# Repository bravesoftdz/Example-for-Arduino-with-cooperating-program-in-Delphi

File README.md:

# Example-for-Arduino-with-cooperating-program-in-Delphi
Example sketch for different Arduino equipment with cooperating program in Delphi for YouTube presentation

This examples I tested for four modules

Arduino Uno + Ethernet shield with expander PCF 8574N port, which is shown in this lesson.
Nodemcu Wifi ESP8266 v2 and v3 (Lolino) - with two expanders PCF8574N Topic of the next lesson
Nodemcu Wifi ESP8266 v2 and v3 (Lolino) - with MCP 23017 16 port expander. In the same lesson you will see the Wemos D1 MINI pro Wifi board as it is compatible with NodeMcu. You just have to make the right adapter. Subject of the next lesson.
Wemos MEGA Wifi plate . - in the plan. The next lesson.

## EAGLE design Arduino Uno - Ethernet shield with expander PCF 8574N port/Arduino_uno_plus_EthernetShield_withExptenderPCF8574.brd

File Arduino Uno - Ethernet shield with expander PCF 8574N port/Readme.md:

Lesson 1. 
  
  by polish Arduino Uno + Ethernet z ekspanderem portów PCF 8574N - ten podkatalog zawiera
           shield dla tych urządzen  i programu exe współpracującym z tym sketch-em .
           Także jest obecne tutaj źródło tego programu w Delphi. Dla tego sketch-u
           jest tutaj dodatkowa bilblioteka do rozszerzenia portów PCF8574 8 portów w 
           postacipliku zip . Uzytkownik może miec kłopty z tą biblioteką .

  by english .Arduino Uno + Ethernet shield with expander PCF 8574N port - this branch contain 
          shield for this equiment and program exe cooerating with this sketch
          also there is present source for program in Delphi . For this is sketch 
          is presnt additional libray for extender PCF8574 8 ports in a zip file . 
          This is because with this libray user can have trouble

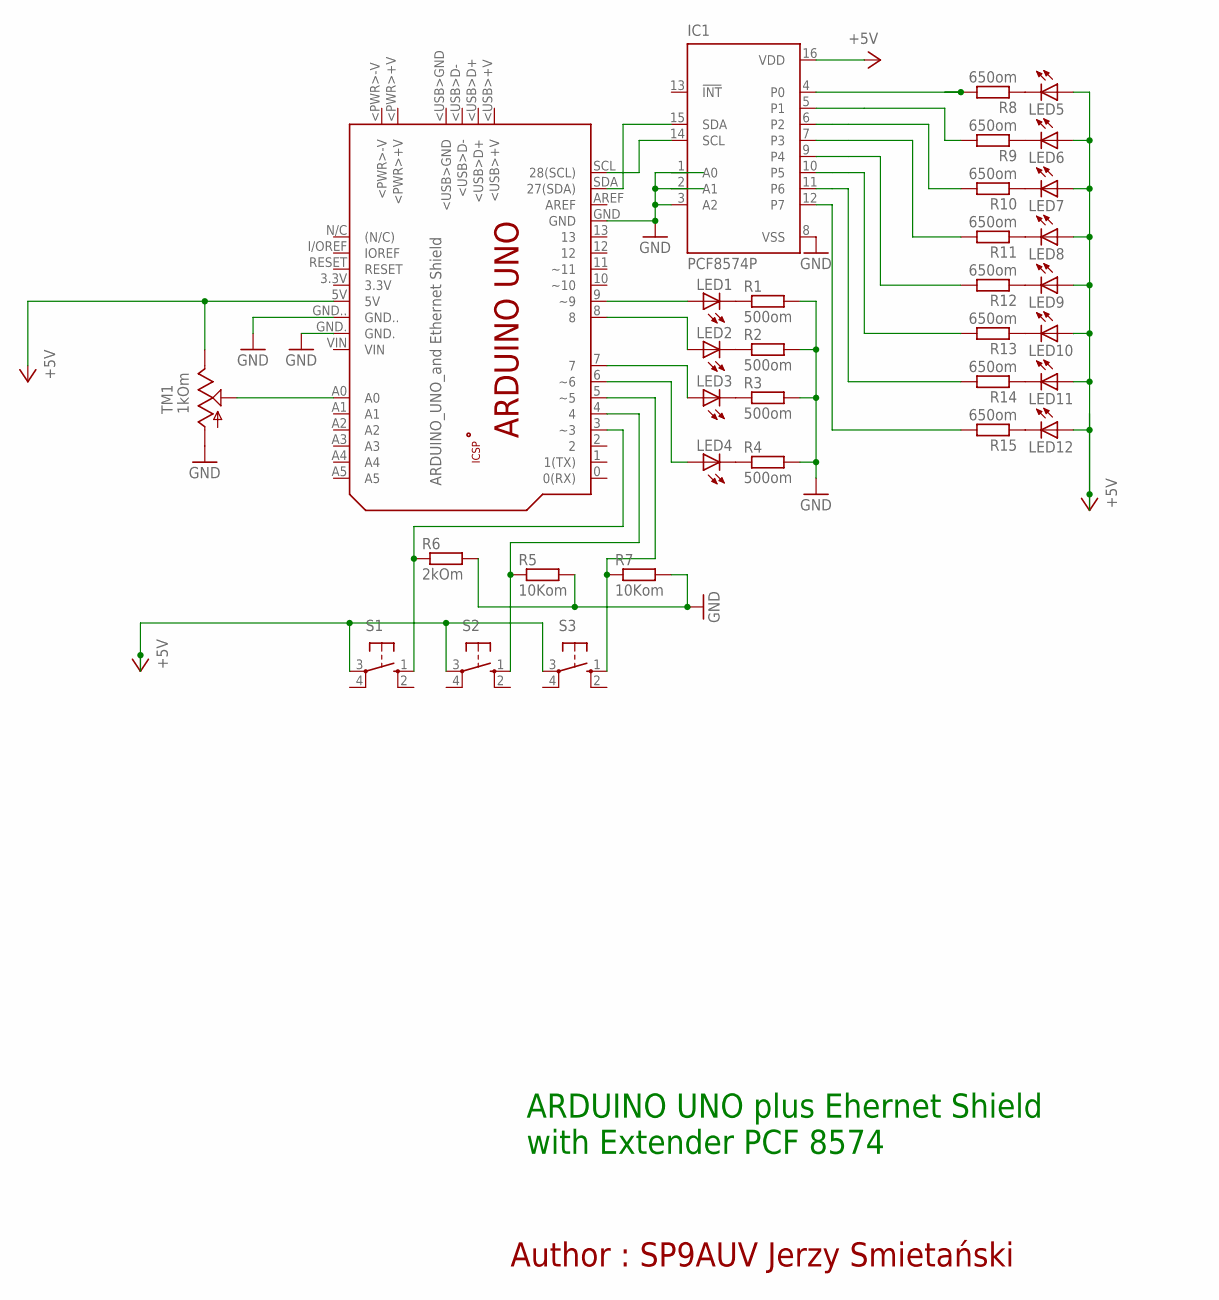
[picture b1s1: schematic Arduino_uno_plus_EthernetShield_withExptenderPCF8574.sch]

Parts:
ARDUINO_UNO: ARDUINO_U1; ARDUINO_UNO
IC1: PCF8574P; DIL16
LED1, LED2, LED3, LED4, LED5, LED6, LED7, LED8, LED9, LED10, LED11, LED12: LEDSQR2X5; LED2X5
R1, R2, R3, R4: 500om; 0204/5
R5, R7: 10Kom; 0204/5
R6: 2kOm; 0204/5
R8, R9, R10, R11, R12, R13, R14, R15: 650om; 0204/5
S1, S2, S3: 10-XX; B3F-10XX
TM1: 1kOm; 6MM

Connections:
+5V: ARDUINO_UNO.5V, IC1.16 (VDD), LED5.A, LED6.A, LED7.A, LED8.A, LED9.A, LED10.A, LED11.A, LED12.A, S1.3, S2.3, S3.3, TM1.E
GND: ARDUINO_UNO.GND, ARDUINO_UNO.GND.., IC1.2 (A1), IC1.3 (A2), IC1.8 (VSS), R1.2, R2.2, R3.2, R4.2, R5.2, R6.2, R7.2
GND1: IC1.5 (P1), R9.2
unnamed: ARDUINO_UNO.A0, TM1.S
unnamed: ARDUINO_UNO.GND., TM1.A
unnamed: LED1.K (C), R1.1
unnamed: LED2.K (C), R2.1
unnamed: LED3.K (C), R3.1
unnamed: LED4.K (C), R4.1
unnamed: ARDUINO_UNO.9 (~9), LED1.A
unnamed: ARDUINO_UNO.8, LED2.A
unnamed: ARDUINO_UNO.7, LED3.A
unnamed: ARDUINO_UNO.3 (~3), R6.1, S1.1 (S)
unnamed: ARDUINO_UNO.6 (~6), LED4.A
unnamed: ARDUINO_UNO.5 (~5), R7.1, S3.1 (S)
unnamed: ARDUINO_UNO.4, R5.1, S2.1 (S)
unnamed: IC1.12 (P7), R15.2
unnamed: IC1.7 (P3), R11.2
unnamed: IC1.6 (P2), R10.2
unnamed: IC1.4 (P0), R8.2
unnamed: LED5.K (C), R8.1
unnamed: LED6.K (C), R9.1
unnamed: LED7.K (C), R10.1
unnamed: LED8.K (C), R11.1
unnamed: IC1.10 (P5), R13.2
unnamed: IC1.9 (P4), R12.2
unnamed: ARDUINO_UNO.SCL (28(SCL)), IC1.14 (SCL)
unnamed: ARDUINO_UNO.SDA (27(SDA)), IC1.15 (SDA)
unnamed: LED9.K (C), R12.1
unnamed: LED10.K (C), R13.1
unnamed: LED11.K (C), R14.1
unnamed: IC1.11 (P6), R14.2
unnamed: LED12.K (C), R15.1

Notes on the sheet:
ARDUINO UNO plus Ehernet Shield with Extender PCF 8574
Author : SP9AUV Jerzy Smietański

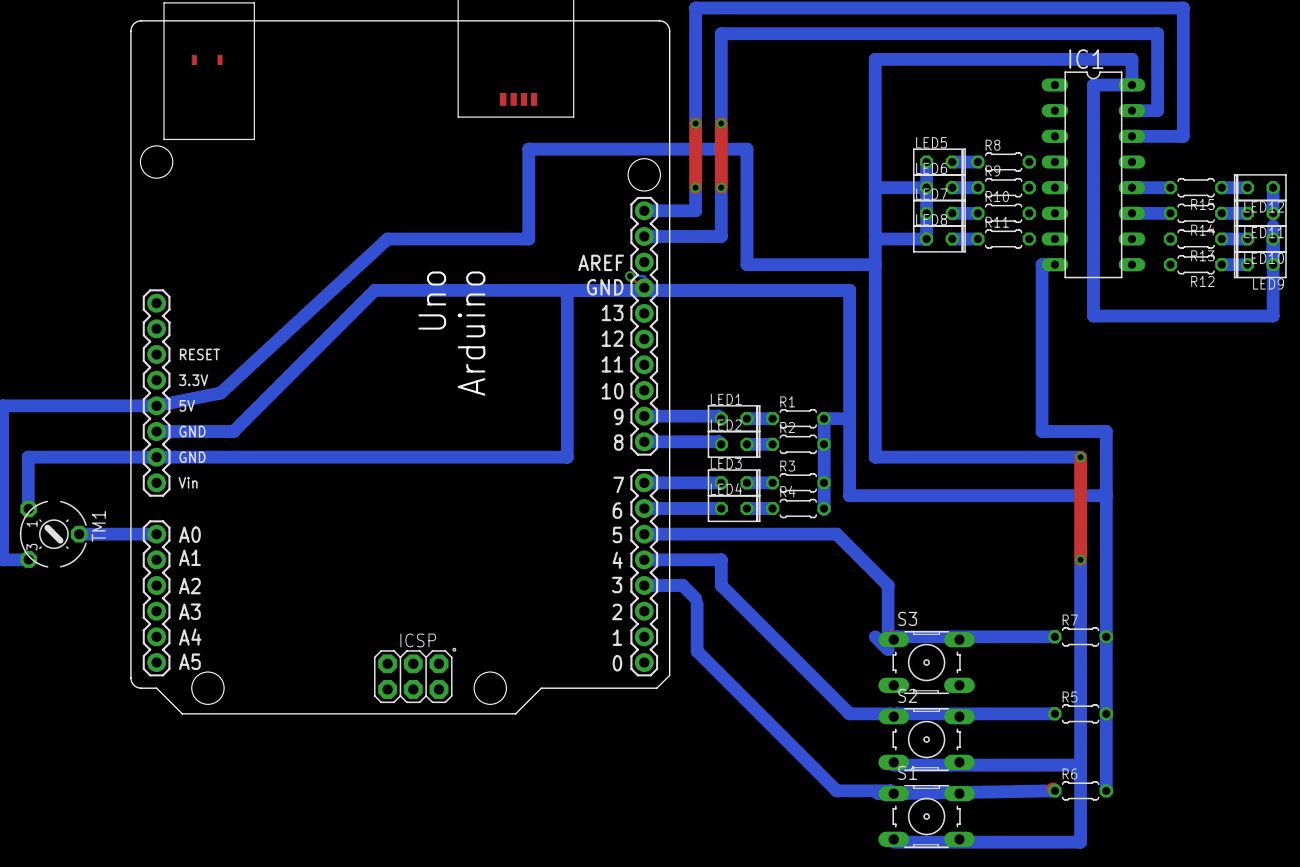
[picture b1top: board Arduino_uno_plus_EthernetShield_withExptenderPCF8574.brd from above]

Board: 2 copper layers, 33 parts (0 on the bottom side), 33 nets.

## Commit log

2017-10-16 To jest konspekt prezentacji w postaci pliku .chm , to jest to co ja mówię w prezentacji na YoTube
2017-10-17 Source in Delphi for program user in a zip file
2017-10-17 File .jpg for show grafic interface user
2017-10-17 Sketch for ChatSer_ethern_with_extend_PCF8574.ino
2017-10-17 Schemat .sch for Eagle
2017-10-17 Board .brd for Eagle
2017-10-17 Schemat in a grafic file when you not have Eagle
2017-10-17 Board .brd in grafic file when you not have Eagle
